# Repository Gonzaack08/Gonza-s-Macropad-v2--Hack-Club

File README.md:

Gonza's Macropad v2:

Second version of the hackpad, hope you like it.

Description:

A simple macropad for gaming, all 4 keycaps and the encoders have diferent characters combinations to use in discord or in game configuration.

## BOM

- 4× Cherry MX Switches
- 2× SK6812 MINI LEDs
- 1× XIAO RP2040
- 4× Blank DSA Keycaps
- 4× M3×16 Bolts
- 4× M3 Heatset Inserts
- 2x EC11 Rotary encoder

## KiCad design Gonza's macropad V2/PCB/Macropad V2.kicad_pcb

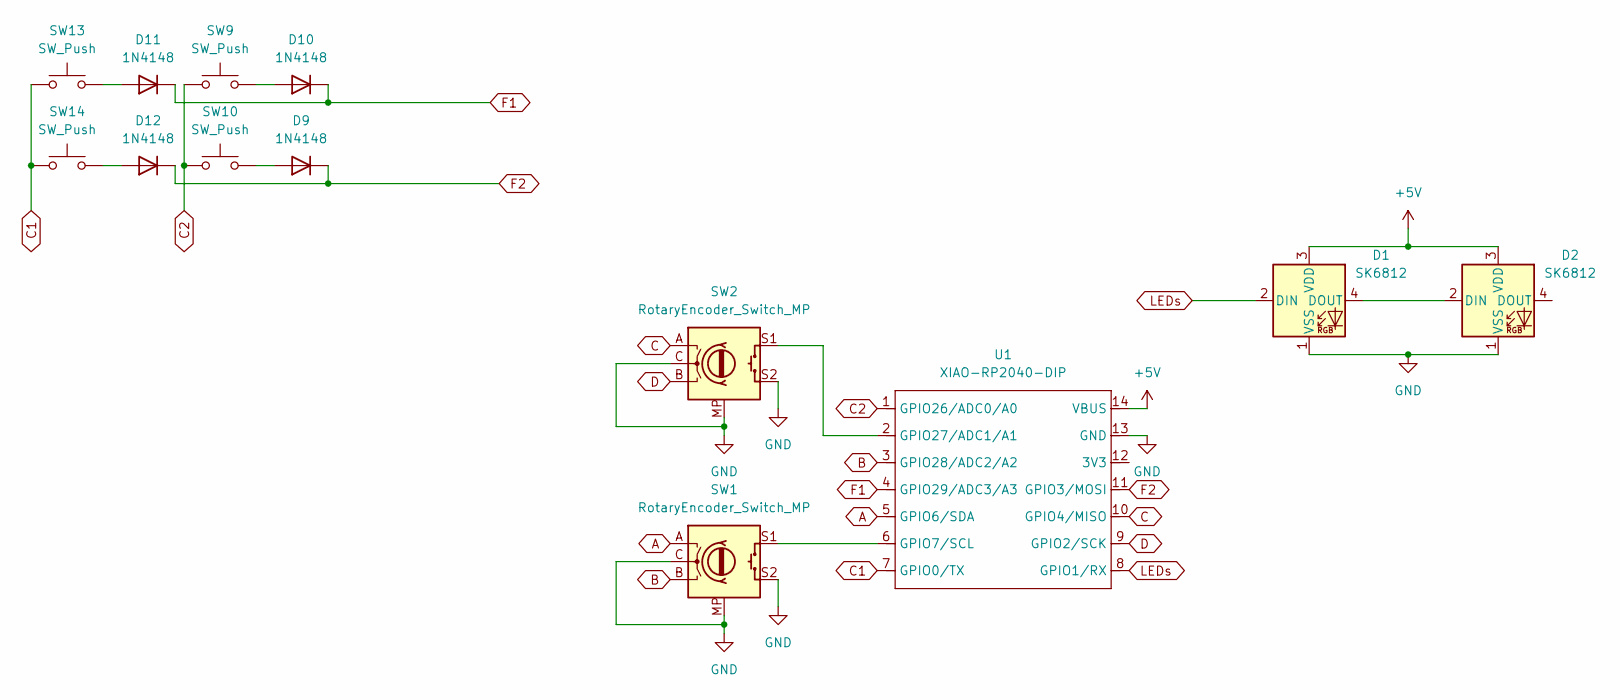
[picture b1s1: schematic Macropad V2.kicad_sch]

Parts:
D1, D2: SK6812; LED_SK6812MINI_PLCC4_3.5x3.5mm_P1.75mm
D9, D10, D11, D12: 1N4148; D_DO-35_SOD27_P7.62mm_Horizontal
SW1, SW2: RotaryEncoder_Switch_MP; RotaryEncoder_Alps_EC11E-Switch_Vertical_H20mm_CircularMoun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
SW9, SW10, SW13, SW14: SW_Push; SW_Cherry_MX_1.00u_PCB
U1: XIAO-RP2040-DIP

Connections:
+5V: D1.3 (VDD), D2.3 (VDD), U1.14 (VBUS)
A: SW1.A, U1.5 (GPIO6/SDA)
B: SW1.B, U1.3 (GPIO28/ADC2/A2)
C: SW2.A, U1.10 (GPIO4/MISO)
C1: SW13.1, SW14.1, U1.7 (GPIO0/TX)
C2: SW9.1, SW10.1, U1.1 (GPIO26/ADC0/A0)
D: SW2.B, U1.9 (GPIO2/SCK)
F1: D10.1 (K), D11.1 (K), U1.4 (GPIO29/ADC3/A3)
F2: D9.1 (K), D12.1 (K), U1.11 (GPIO3/MOSI)
GND: D1.1 (VSS), D2.1 (VSS), SW1.C, SW1.MP, SW1.S2, SW2.C, SW2.MP, SW2.S2, U1.13 (GND)
LEDs: D1.2 (DIN), U1.8 (GPIO1/RX)
unnamed: D1.4 (DOUT), D2.2 (DIN)
unnamed: D9.2 (A), SW10.2
unnamed: D10.2 (A), SW9.2
unnamed: D11.2 (A), SW13.2
unnamed: D12.2 (A), SW14.2
unnamed: SW1.S1, U1.6 (GPIO7/SCL)
unnamed: SW2.S1, U1.2 (GPIO27/ADC1/A1)

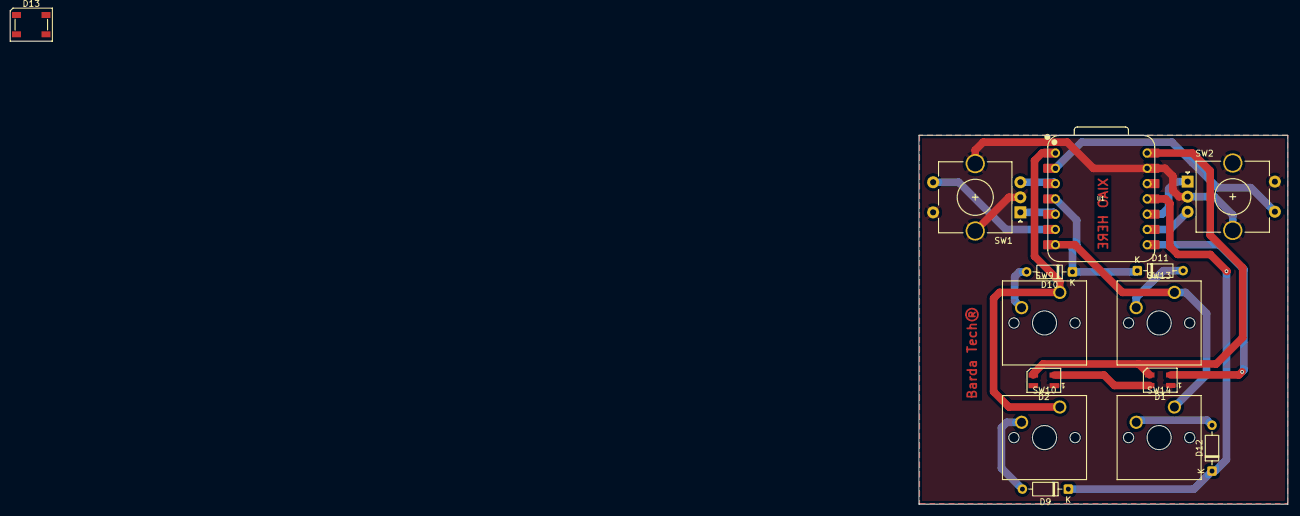
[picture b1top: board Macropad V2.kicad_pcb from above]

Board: 2 copper layers, 61.3 x 61.3 mm, 14 parts (0 on the bottom side), 18 nets.

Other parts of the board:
D13: SK6812; LED_SK6812_PLCC4_5.0x5.0mm_P3.2mm

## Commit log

2026-03-31 Update README with project details and BOM
    Added detailed description and BOM for Gonza's Macropad v2.
2026-03-31 Add images to README for macropad
    Added images to enhance the README with visuals of the macropad.
